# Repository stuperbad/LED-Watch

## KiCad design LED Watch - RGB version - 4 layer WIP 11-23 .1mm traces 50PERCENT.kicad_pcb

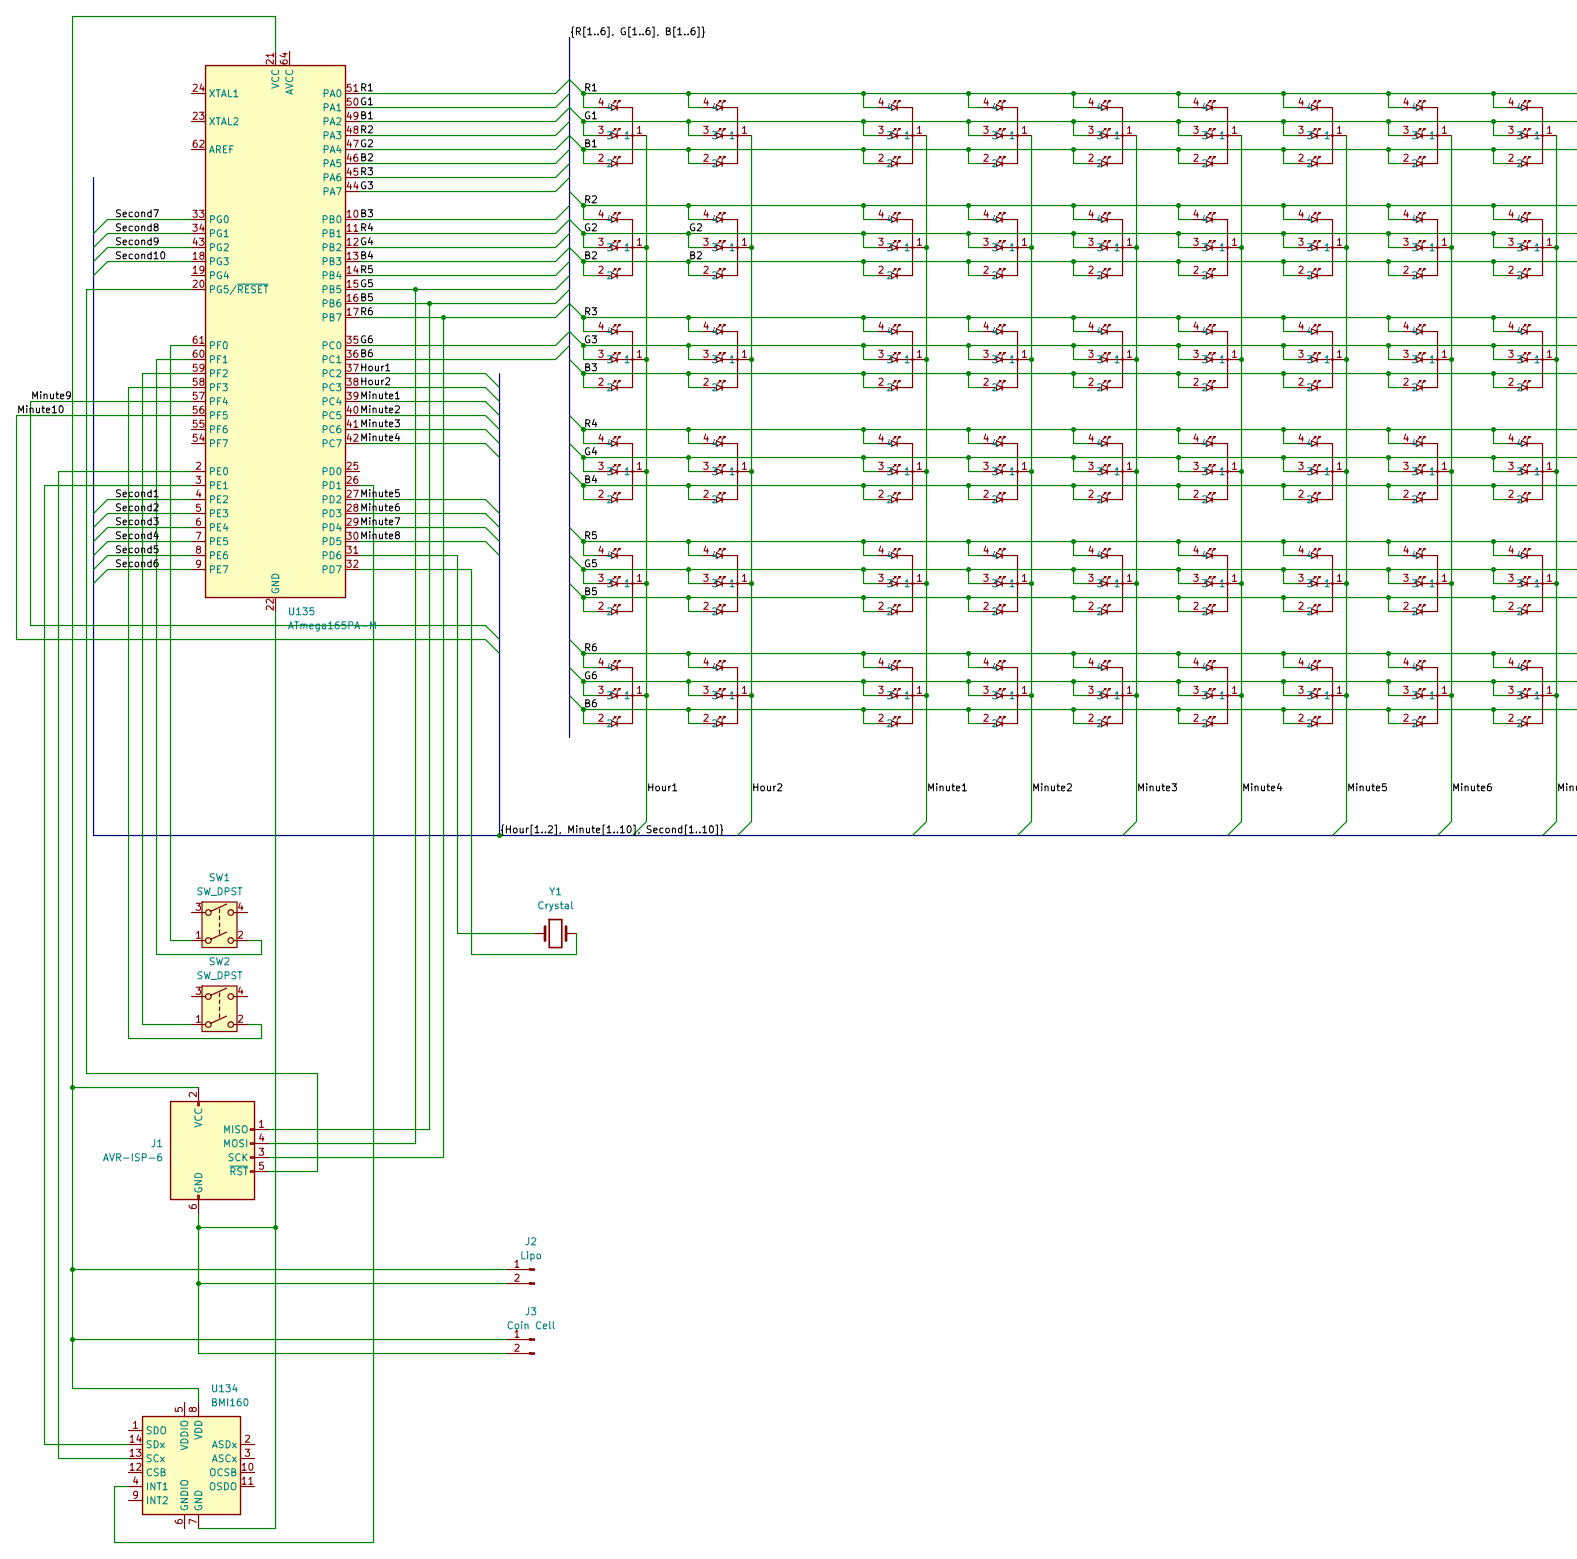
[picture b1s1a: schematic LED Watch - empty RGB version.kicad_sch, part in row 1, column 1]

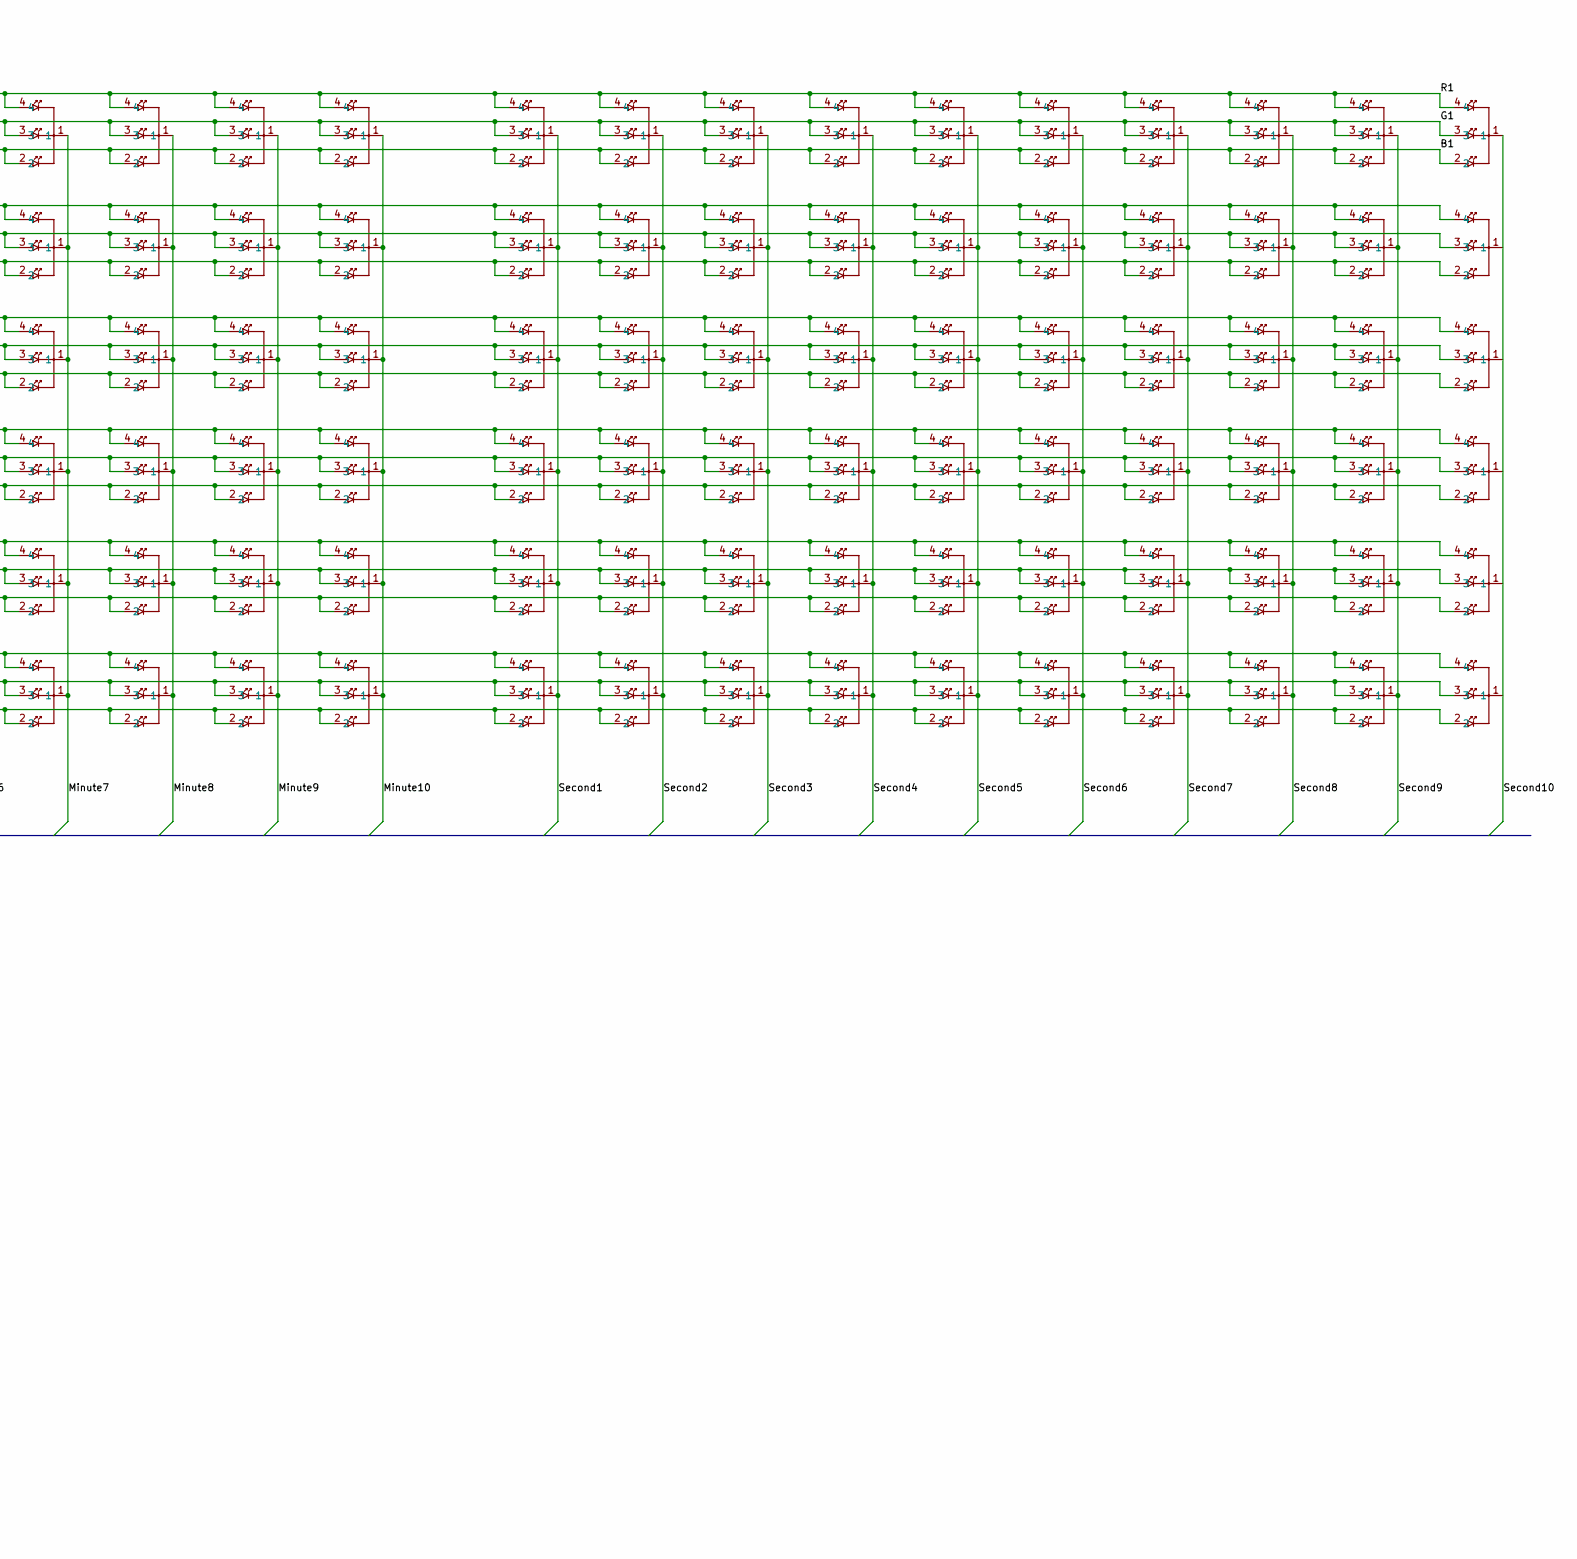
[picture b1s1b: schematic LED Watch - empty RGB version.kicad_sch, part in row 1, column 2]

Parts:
J1: AVR-ISP-6; JST_SH_BM05B-SRSS-TB_1x05-1MP_P1.00mm_Vertical
J2: Lipo; JST_SH_SM02B-SRSS-TB_1x02-1MP_P1.00mm_Horizontal
J3: Coin Cell; BatteryHolder_Keystone_3034_1x20mm
SW1, SW2: SW_DPST; SW_TS21-34-035-BK-260-SMT-TR
U2, U3, U4, U5, U6, U7, U8, U9, U10, U11, U12, U13, U14, U15, U16, U17, U18, U19, U20, U21, U22, U23, U24, U25, U26, U27, U28, U29, U30, U31, U32, U33, U34, U35, U36, U37, U38, U39, U40, U41, U42, U43, U44, U45, U46, U47, U48, U49, U50, U51, U52, U53, U54, U55, U56, U57, U58, U59, U60, U61, U62, U63, U64, U65, U66, U67, U68, U69, U70, U71, U72, U73, U74, U75, U76, U77, U78, U79, U80, U81, U82, U83, U84, U85, U86, U87, U88, U89, U90, U91, U92, U93, U94, U95, U96, U97, U98, U99, U100, U101, U102, U103, U104, U105, U106, U107, U108, U109, U110, U111, U112, U113, U114, U115, U116, U117, U118, U119, U120, U121, U122, U123, U124, U125, U126, U127, U128, U129, U130, U131, U132, U133: B39D3RGB-F6C0001HOU1930; B39D3RGB-F6C0001HOU1930_HVK; MPN LTST-C19HE1WT; Digi-Key_PN 160-2162-1-ND
U134: BMI160; Bosch_LGA-14_3x2.5mm_P0.5mm
U135: ATmega165PA-M; QFN-64-1EP_9x9mm_P0.5mm_EP5.4x5.4mm
Y1: Crystal; Crystal_SMD_3215-2Pin_3.2x1.5mm

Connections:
/B1: U2.2, U8.2, U14.2, U20.2, U26.2, U32.2, U38.2, U44.2, U50.2, U56.2, U62.2, U68.2, U74.2, U80.2, U86.2, U92.2, U98.2, U104.2, U110.2, U116.2, U122.2, U128.2, U135.49 (PA2)
/B2: U3.2, U9.2, U15.2, U21.2, U27.2, U33.2, U39.2, U45.2, U51.2, U57.2, U63.2, U69.2, U75.2, U81.2, U87.2, U93.2, U99.2, U105.2, U111.2, U117.2, U123.2, U129.2, U135.46 (PA5)
/B3: U4.2, U10.2, U16.2, U22.2, U28.2, U34.2, U40.2, U46.2, U52.2, U58.2, U64.2, U70.2, U76.2, U82.2, U88.2, U94.2, U100.2, U106.2, U112.2, U118.2, U124.2, U130.2, U135.10 (PB0)
/B4: U5.2, U11.2, U17.2, U23.2, U29.2, U35.2, U41.2, U47.2, U53.2, U59.2, U65.2, U71.2, U77.2, U83.2, U89.2, U95.2, U101.2, U107.2, U113.2, U119.2, U125.2, U131.2, U135.13 (PB3)
/B5: J1.1 (MISO), U6.2, U12.2, U18.2, U24.2, U30.2, U36.2, U42.2, U48.2, U54.2, U60.2, U66.2, U72.2, U78.2, U84.2, U90.2, U96.2, U102.2, U108.2, U114.2, U120.2, U126.2, U132.2, U135.16 (PB6)
/B6: U7.2, U13.2, U19.2, U25.2, U31.2, U37.2, U43.2, U49.2, U55.2, U61.2, U67.2, U73.2, U79.2, U85.2, U91.2, U97.2, U103.2, U109.2, U115.2, U121.2, U127.2, U133.2, U135.36 (PC1)
/G1: U2.3, U8.3, U14.3, U20.3, U26.3, U32.3, U38.3, U44.3, U50.3, U56.3, U62.3, U68.3, U74.3, U80.3, U86.3, U92.3, U98.3, U104.3, U110.3, U116.3, U122.3, U128.3, U135.50 (PA1)
/G2: U3.3, U9.3, U15.3, U21.3, U27.3, U33.3, U39.3, U45.3, U51.3, U57.3, U63.3, U69.3, U75.3, U81.3, U87.3, U93.3, U99.3, U105.3, U111.3, U117.3, U123.3, U129.3, U135.47 (PA4)
/G3: U4.3, U10.3, U16.3, U22.3, U28.3, U34.3, U40.3, U46.3, U52.3, U58.3, U64.3, U70.3, U76.3, U82.3, U88.3, U94.3, U100.3, U106.3, U112.3, U118.3, U124.3, U130.3, U135.44 (PA7)
/G4: U5.3, U11.3, U17.3, U23.3, U29.3, U35.3, U41.3, U47.3, U53.3, U59.3, U65.3, U71.3, U77.3, U83.3, U89.3, U95.3, U101.3, U107.3, U113.3, U119.3, U125.3, U131.3, U135.12 (PB2)
/G5: J1.4 (MOSI), U6.3, U12.3, U18.3, U24.3, U30.3, U36.3, U42.3, U48.3, U54.3, U60.3, U66.3, U72.3, U78.3, U84.3, U90.3, U96.3, U102.3, U108.3, U114.3, U120.3, U126.3, U132.3, U135.15 (PB5)
/G6: U7.3, U13.3, U19.3, U25.3, U31.3, U37.3, U43.3, U49.3, U55.3, U61.3, U67.3, U73.3, U79.3, U85.3, U91.3, U97.3, U103.3, U109.3, U115.3, U121.3, U127.3, U133.3, U135.35 (PC0)
/Hour1: U2.1, U3.1, U4.1, U5.1, U6.1, U7.1, U135.37 (PC2)
/Hour2: U8.1, U9.1, U10.1, U11.1, U12.1, U13.1, U135.38 (PC3)
/Minute1: U14.1, U15.1, U16.1, U17.1, U18.1, U19.1, U135.39 (PC4)
/Minute2: U20.1, U21.1, U22.1, U23.1, U24.1, U25.1, U135.40 (PC5)
/Minute3: U26.1, U27.1, U28.1, U29.1, U30.1, U31.1, U135.41 (PC6)
/Minute4: U32.1, U33.1, U34.1, U35.1, U36.1, U37.1, U135.42 (PC7)
/Minute5: U38.1, U39.1, U40.1, U41.1, U42.1, U43.1, U135.27 (PD2)
/Minute6: U44.1, U45.1, U46.1, U47.1, U48.1, U49.1, U135.28 (PD3)
/Minute7: U50.1, U51.1, U52.1, U53.1, U54.1, U55.1, U135.29 (PD4)
/Minute8: U56.1, U57.1, U58.1, U59.1, U60.1, U61.1, U135.30 (PD5)
/Minute9: U62.1, U63.1, U64.1, U65.1, U66.1, U67.1, U135.57 (PF4)
/Minute10: U68.1, U69.1, U70.1, U71.1, U72.1, U73.1, U135.56 (PF5)
/R1: U2.4, U8.4, U14.4, U20.4, U26.4, U32.4, U38.4, U44.4, U50.4, U56.4, U62.4, U68.4, U74.4, U80.4, U86.4, U92.4, U98.4, U104.4, U110.4, U116.4, U122.4, U128.4, U135.51 (PA0)
/R2: U3.4, U9.4, U15.4, U21.4, U27.4, U33.4, U39.4, U45.4, U51.4, U57.4, U63.4, U69.4, U75.4, U81.4, U87.4, U93.4, U99.4, U105.4, U111.4, U117.4, U123.4, U129.4, U135.48 (PA3)
/R3: U4.4, U10.4, U16.4, U22.4, U28.4, U34.4, U40.4, U46.4, U52.4, U58.4, U64.4, U70.4, U76.4, U82.4, U88.4, U94.4, U100.4, U106.4, U112.4, U118.4, U124.4, U130.4, U135.45 (PA6)
/R4: U5.4, U11.4, U17.4, U23.4, U29.4, U35.4, U41.4, U47.4, U53.4, U59.4, U65.4, U71.4, U77.4, U83.4, U89.4, U95.4, U101.4, U107.4, U113.4, U119.4, U125.4, U131.4, U135.11 (PB1)
/R5: U6.4, U12.4, U18.4, U24.4, U30.4, U36.4, U42.4, U48.4, U54.4, U60.4, U66.4, U72.4, U78.4, U84.4, U90.4, U96.4, U102.4, U108.4, U114.4, U120.4, U126.4, U132.4, U135.14 (PB4)
/R6: J1.3 (SCK), U7.4, U13.4, U19.4, U25.4, U31.4, U37.4, U43.4, U49.4, U55.4, U61.4, U67.4, U73.4, U79.4, U85.4, U91.4, U97.4, U103.4, U109.4, U115.4, U121.4, U127.4, U133.4, U135.17 (PB7)
/Second1: U74.1, U75.1, U76.1, U77.1, U78.1, U79.1, U135.4 (PE2)
/Second2: U80.1, U81.1, U82.1, U83.1, U84.1, U85.1, U135.5 (PE3)
/Second3: U86.1, U87.1, U88.1, U89.1, U90.1, U91.1, U135.6 (PE4)
/Second4: U92.1, U93.1, U94.1, U95.1, U96.1, U97.1, U135.7 (PE5)
/Second5: U98.1, U99.1, U100.1, U101.1, U102.1, U103.1, U135.8 (PE6)
/Second6: U104.1, U105.1, U106.1, U107.1, U108.1, U109.1, U135.9 (PE7)
/Second7: U110.1, U111.1, U112.1, U113.1, U114.1, U115.1, U135.33 (PG0)
/Second8: U116.1, U117.1, U118.1, U119.1, U120.1, U121.1, U135.34 (PG1)
/Second9: U122.1, U123.1, U124.1, U125.1, U126.1, U127.1, U135.43 (PG2)
/Second10: U128.1, U129.1, U130.1, U131.1, U132.1, U133.1, U135.18 (PG3)
unnamed: J1.2 (VCC), J2.1, J3.1, U134.8 (VDD), U135.21 (VCC), U135.52 (VCC)
unnamed: J1.5 (~RST), U135.20 (PG5/~RESET)
unnamed: U134.4 (INT1), U135.26 (PD1)
unnamed: U134.13 (SCx), U135.2 (PE0)
unnamed: U134.14 (SDx), U135.3 (PE1)
unnamed: SW1.1, U135.61 (PF0)
unnamed: SW1.2, U135.60 (PF1)
unnamed: SW2.1, U135.59 (PF2)
unnamed: SW2.2, U135.58 (PF3)

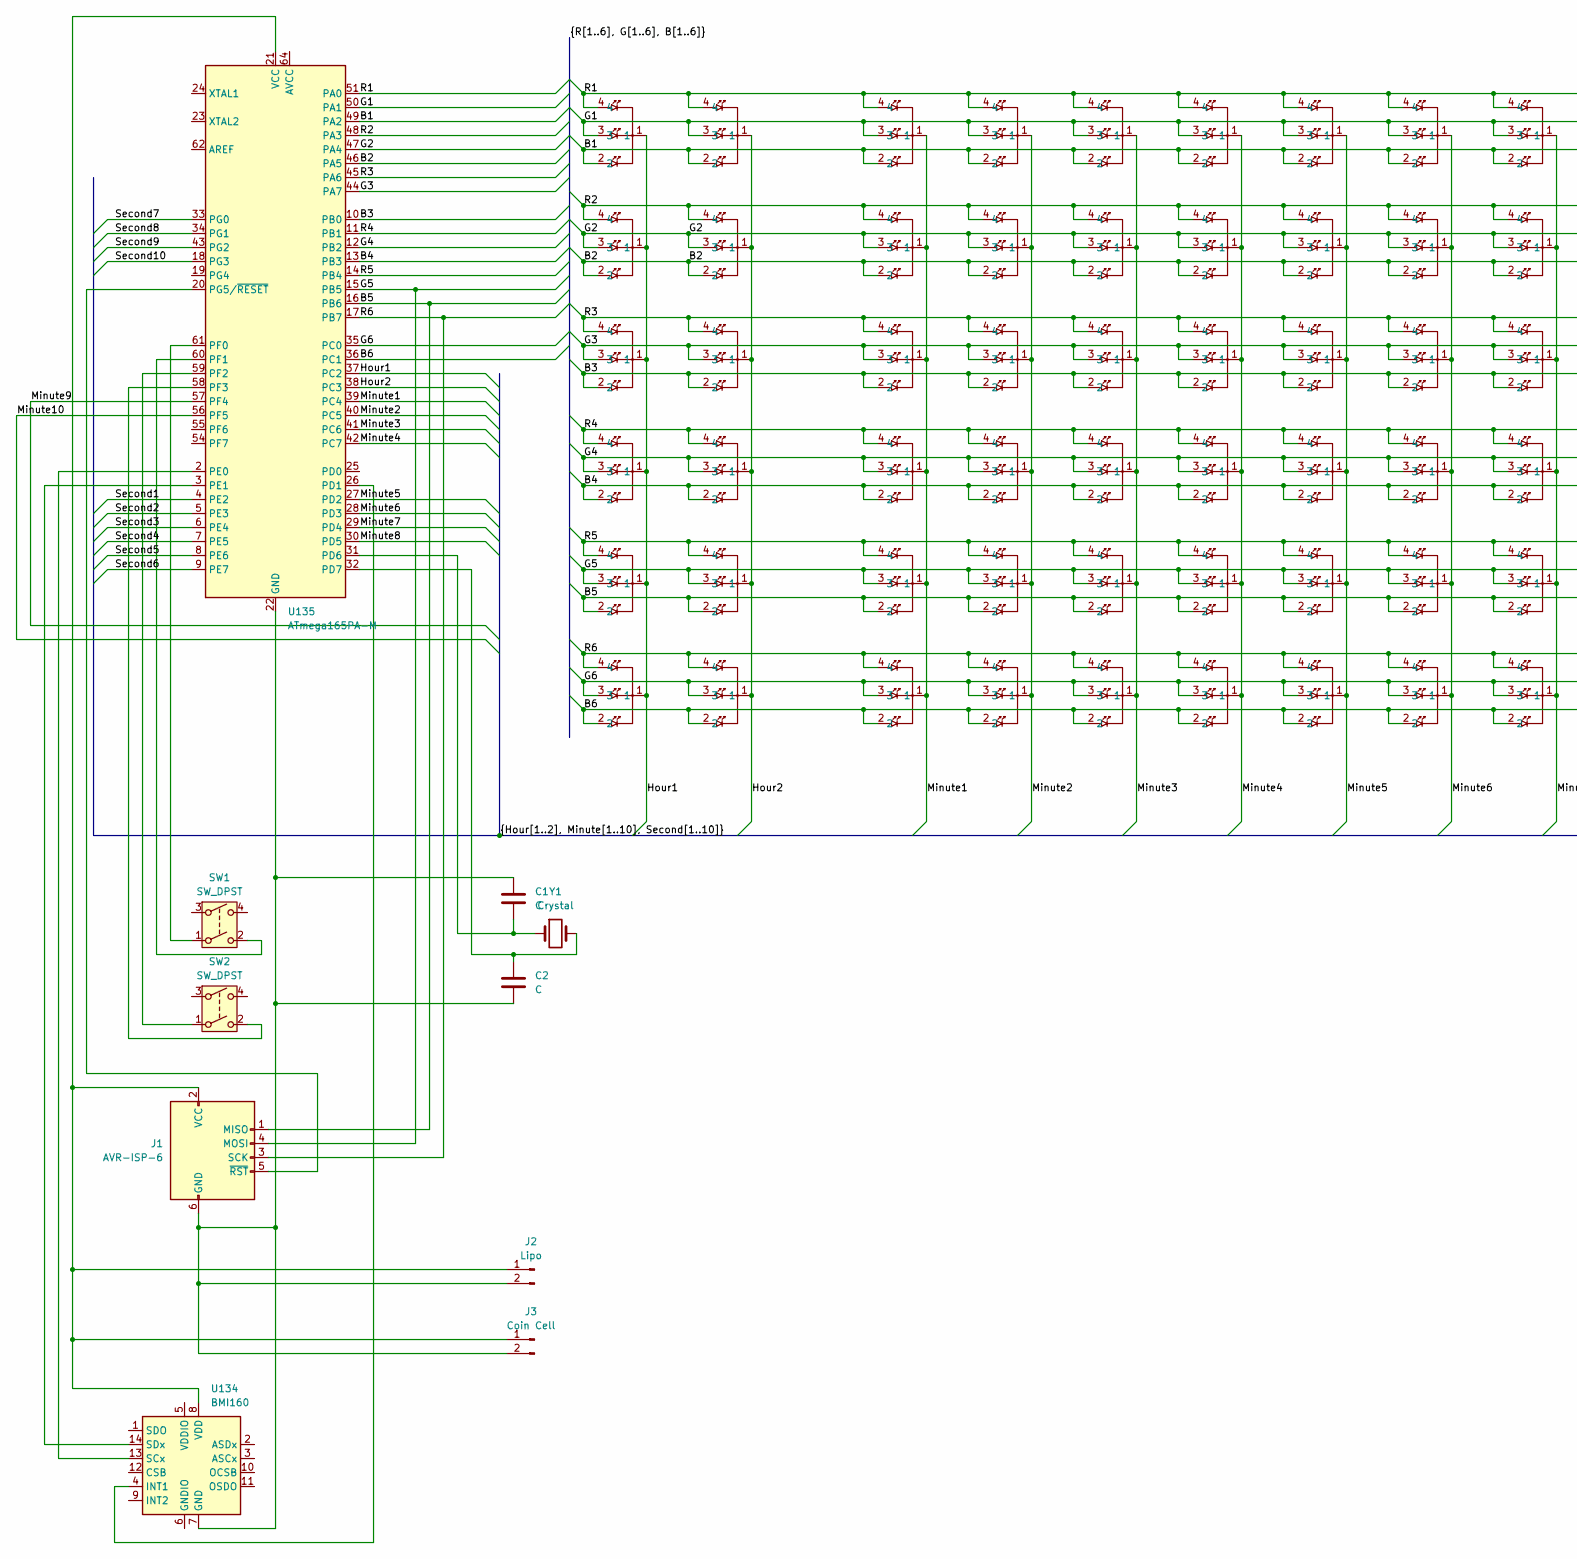
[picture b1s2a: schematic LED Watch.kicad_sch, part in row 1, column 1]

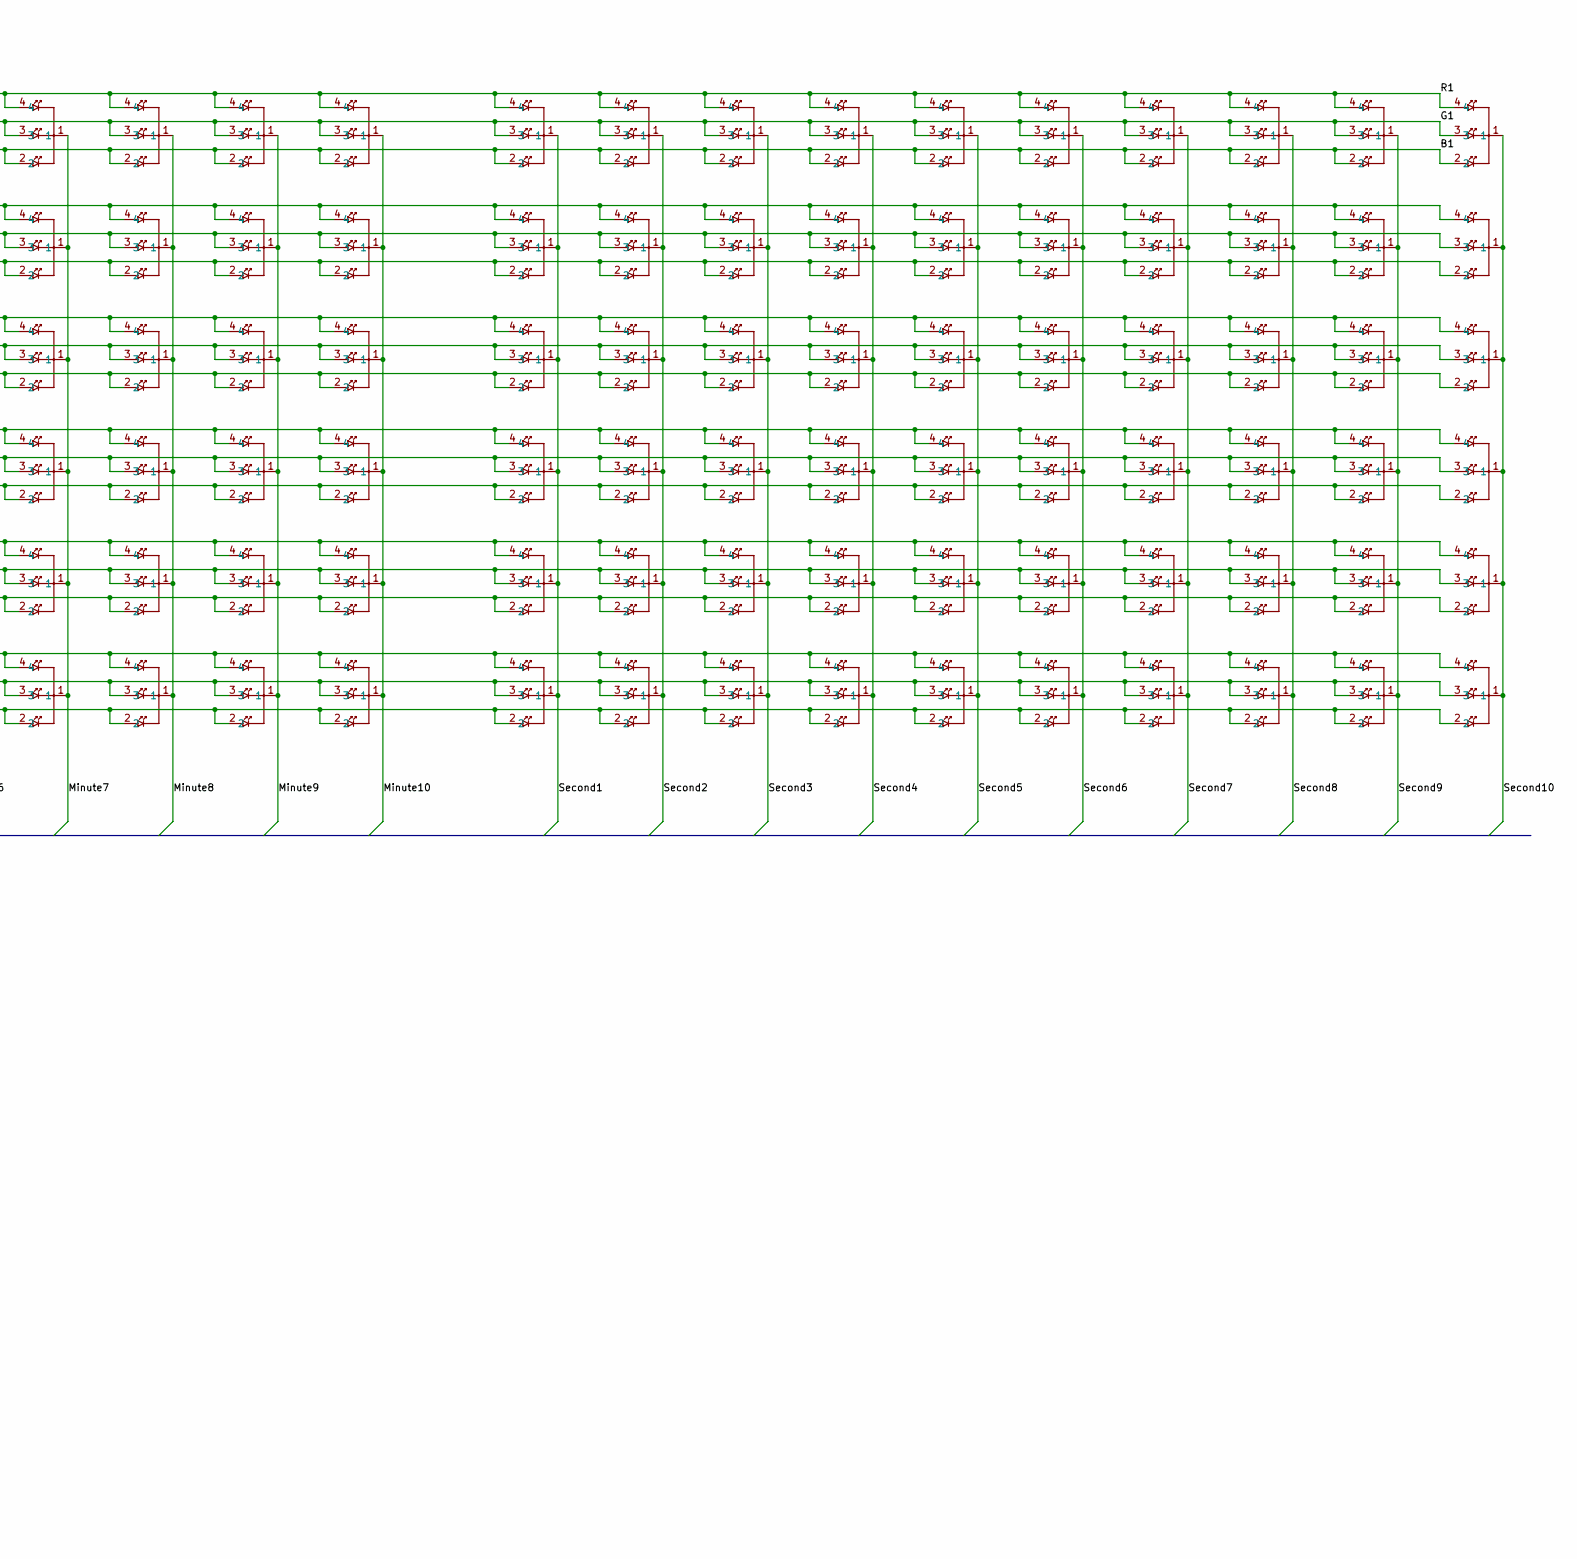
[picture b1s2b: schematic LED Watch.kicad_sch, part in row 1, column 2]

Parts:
C1, C2: C; C_0201_0603Metric
J1: AVR-ISP-6; Tag-Connect_TC2030-IDC-NL_2x03_P1.27mm_Vertical
J2: Lipo; JST_SH_SM02B-SRSS-TB_1x02-1MP_P1.00mm_Horizontal
J3: Coin Cell; BatteryHolder_Keystone_3034_1x20mm
SW1, SW2: SW_DPST; SW_TS21-34-035-BK-260-SMT-TR
U2, U3, U4, U5, U6, U7, U8, U9, U10, U11, U12, U13, U14, U15, U16, U17, U18, U19, U20, U21, U22, U23, U24, U25, U26, U27, U28, U29, U30, U31, U32, U33, U34, U35, U36, U37, U38, U39, U40, U41, U42, U43, U44, U45, U46, U47, U48, U49, U50, U51, U52, U53, U54, U55, U56, U57, U58, U59, U60, U61, U62, U63, U64, U65, U66, U67, U68, U69, U70, U71, U72, U73, U74, U75, U76, U77, U78, U79, U80, U81, U82, U83, U84, U85, U86, U87, U88, U89, U90, U91, U92, U93, U94, U95, U96, U97, U98, U99, U100, U101, U102, U103, U104, U105, U106, U107, U108, U109, U110, U111, U112, U113, U114, U115, U116, U117, U118, U119, U120, U121, U122, U123, U124, U125, U126, U127, U128, U129, U130, U131, U132, U133: B39D3RGB-F6C0001HOU1930; B39D3RGB-F6C0001HOU1930_HVK; MPN LTST-C19HE1WT; Digi-Key_PN 160-2162-1-ND
U134: BMI160; Bosch_LGA-14_3x2.5mm_P0.5mm
U135: ATmega165PA-M; QFN-64-1EP_9x9mm_P0.5mm_EP5.4x5.4mm
Y1: Crystal; Crystal_SMD_3215-2Pin_3.2x1.5mm

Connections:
/B1: U2.2, U8.2, U14.2, U20.2, U26.2, U32.2, U38.2, U44.2, U50.2, U56.2, U62.2, U68.2, U74.2, U80.2, U86.2, U92.2, U98.2, U104.2, U110.2, U116.2, U122.2, U128.2, U135.49 (PA2)
/B2: U3.2, U9.2, U15.2, U21.2, U27.2, U33.2, U39.2, U45.2, U51.2, U57.2, U63.2, U69.2, U75.2, U81.2, U87.2, U93.2, U99.2, U105.2, U111.2, U117.2, U123.2, U129.2, U135.46 (PA5)
/B3: U4.2, U10.2, U16.2, U22.2, U28.2, U34.2, U40.2, U46.2, U52.2, U58.2, U64.2, U70.2, U76.2, U82.2, U88.2, U94.2, U100.2, U106.2, U112.2, U118.2, U124.2, U130.2, U135.10 (PB0)
/B4: U5.2, U11.2, U17.2, U23.2, U29.2, U35.2, U41.2, U47.2, U53.2, U59.2, U65.2, U71.2, U77.2, U83.2, U89.2, U95.2, U101.2, U107.2, U113.2, U119.2, U125.2, U131.2, U135.13 (PB3)
/B5: J1.1 (MISO), U6.2, U12.2, U18.2, U24.2, U30.2, U36.2, U42.2, U48.2, U54.2, U60.2, U66.2, U72.2, U78.2, U84.2, U90.2, U96.2, U102.2, U108.2, U114.2, U120.2, U126.2, U132.2, U135.16 (PB6)
/B6: U7.2, U13.2, U19.2, U25.2, U31.2, U37.2, U43.2, U49.2, U55.2, U61.2, U67.2, U73.2, U79.2, U85.2, U91.2, U97.2, U103.2, U109.2, U115.2, U121.2, U127.2, U133.2, U135.36 (PC1)
/G1: U2.3, U8.3, U14.3, U20.3, U26.3, U32.3, U38.3, U44.3, U50.3, U56.3, U62.3, U68.3, U74.3, U80.3, U86.3, U92.3, U98.3, U104.3, U110.3, U116.3, U122.3, U128.3, U135.50 (PA1)
/G2: U3.3, U9.3, U15.3, U21.3, U27.3, U33.3, U39.3, U45.3, U51.3, U57.3, U63.3, U69.3, U75.3, U81.3, U87.3, U93.3, U99.3, U105.3, U111.3, U117.3, U123.3, U129.3, U135.47 (PA4)
/G3: U4.3, U10.3, U16.3, U22.3, U28.3, U34.3, U40.3, U46.3, U52.3, U58.3, U64.3, U70.3, U76.3, U82.3, U88.3, U94.3, U100.3, U106.3, U112.3, U118.3, U124.3, U130.3, U135.44 (PA7)
/G4: U5.3, U11.3, U17.3, U23.3, U29.3, U35.3, U41.3, U47.3, U53.3, U59.3, U65.3, U71.3, U77.3, U83.3, U89.3, U95.3, U101.3, U107.3, U113.3, U119.3, U125.3, U131.3, U135.12 (PB2)
/G5: J1.4 (MOSI), U6.3, U12.3, U18.3, U24.3, U30.3, U36.3, U42.3, U48.3, U54.3, U60.3, U66.3, U72.3, U78.3, U84.3, U90.3, U96.3, U102.3, U108.3, U114.3, U120.3, U126.3, U132.3, U135.15 (PB5)
/G6: U7.3, U13.3, U19.3, U25.3, U31.3, U37.3, U43.3, U49.3, U55.3, U61.3, U67.3, U73.3, U79.3, U85.3, U91.3, U97.3, U103.3, U109.3, U115.3, U121.3, U127.3, U133.3, U135.35 (PC0)
/Hour1: U2.1, U3.1, U4.1, U5.1, U6.1, U7.1, U135.37 (PC2)
/Hour2: U8.1, U9.1, U10.1, U11.1, U12.1, U13.1, U135.38 (PC3)
/Minute1: U14.1, U15.1, U16.1, U17.1, U18.1, U19.1, U135.39 (PC4)
/Minute2: U20.1, U21.1, U22.1, U23.1, U24.1, U25.1, U135.40 (PC5)
/Minute3: U26.1, U27.1, U28.1, U29.1, U30.1, U31.1, U135.41 (PC6)
/Minute4: U32.1, U33.1, U34.1, U35.1, U36.1, U37.1, U135.42 (PC7)
/Minute5: U38.1, U39.1, U40.1, U41.1, U42.1, U43.1, U135.27 (PD2)
/Minute6: U44.1, U45.1, U46.1, U47.1, U48.1, U49.1, U135.28 (PD3)
/Minute7: U50.1, U51.1, U52.1, U53.1, U54.1, U55.1, U135.29 (PD4)
/Minute8: U56.1, U57.1, U58.1, U59.1, U60.1, U61.1, U135.30 (PD5)
/Minute9: U62.1, U63.1, U64.1, U65.1, U66.1, U67.1, U135.57 (PF4)
/Minute10: U68.1, U69.1, U70.1, U71.1, U72.1, U73.1, U135.56 (PF5)
/R1: U2.4, U8.4, U14.4, U20.4, U26.4, U32.4, U38.4, U44.4, U50.4, U56.4, U62.4, U68.4, U74.4, U80.4, U86.4, U92.4, U98.4, U104.4, U110.4, U116.4, U122.4, U128.4, U135.51 (PA0)
/R2: U3.4, U9.4, U15.4, U21.4, U27.4, U33.4, U39.4, U45.4, U51.4, U57.4, U63.4, U69.4, U75.4, U81.4, U87.4, U93.4, U99.4, U105.4, U111.4, U117.4, U123.4, U129.4, U135.48 (PA3)
/R3: U4.4, U10.4, U16.4, U22.4, U28.4, U34.4, U40.4, U46.4, U52.4, U58.4, U64.4, U70.4, U76.4, U82.4, U88.4, U94.4, U100.4, U106.4, U112.4, U118.4, U124.4, U130.4, U135.45 (PA6)
/R4: U5.4, U11.4, U17.4, U23.4, U29.4, U35.4, U41.4, U47.4, U53.4, U59.4, U65.4, U71.4, U77.4, U83.4, U89.4, U95.4, U101.4, U107.4, U113.4, U119.4, U125.4, U131.4, U135.11 (PB1)
/R5: U6.4, U12.4, U18.4, U24.4, U30.4, U36.4, U42.4, U48.4, U54.4, U60.4, U66.4, U72.4, U78.4, U84.4, U90.4, U96.4, U102.4, U108.4, U114.4, U120.4, U126.4, U132.4, U135.14 (PB4)
/R6: J1.3 (SCK), U7.4, U13.4, U19.4, U25.4, U31.4, U37.4, U43.4, U49.4, U55.4, U61.4, U67.4, U73.4, U79.4, U85.4, U91.4, U97.4, U103.4, U109.4, U115.4, U121.4, U127.4, U133.4, U135.17 (PB7)
/Second1: U74.1, U75.1, U76.1, U77.1, U78.1, U79.1, U135.4 (PE2)
/Second2: U80.1, U81.1, U82.1, U83.1, U84.1, U85.1, U135.5 (PE3)
/Second3: U86.1, U87.1, U88.1, U89.1, U90.1, U91.1, U135.6 (PE4)
/Second4: U92.1, U93.1, U94.1, U95.1, U96.1, U97.1, U135.7 (PE5)
/Second5: U98.1, U99.1, U100.1, U101.1, U102.1, U103.1, U135.8 (PE6)
/Second6: U104.1, U105.1, U106.1, U107.1, U108.1, U109.1, U135.9 (PE7)
/Second7: U110.1, U111.1, U112.1, U113.1, U114.1, U115.1, U135.33 (PG0)
/Second8: U116.1, U117.1, U118.1, U119.1, U120.1, U121.1, U135.34 (PG1)
/Second9: U122.1, U123.1, U124.1, U125.1, U126.1, U127.1, U135.43 (PG2)
/Second10: U128.1, U129.1, U130.1, U131.1, U132.1, U133.1, U135.18 (PG3)
unnamed: J1.2 (VCC), J2.1, J3.1, U134.8 (VDD), U135.21 (VCC), U135.52 (VCC)
unnamed: J1.5 (~RST), U135.20 (PG5/~RESET)
unnamed: U134.4 (INT1), U135.26 (PD1)
unnamed: U134.13 (SCx), U135.2 (PE0)
unnamed: U134.14 (SDx), U135.3 (PE1)
unnamed: SW1.1, U135.61 (PF0)
unnamed: SW1.2, U135.60 (PF1)
unnamed: SW2.1, U135.59 (PF2)
unnamed: SW2.2, U135.58 (PF3)

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
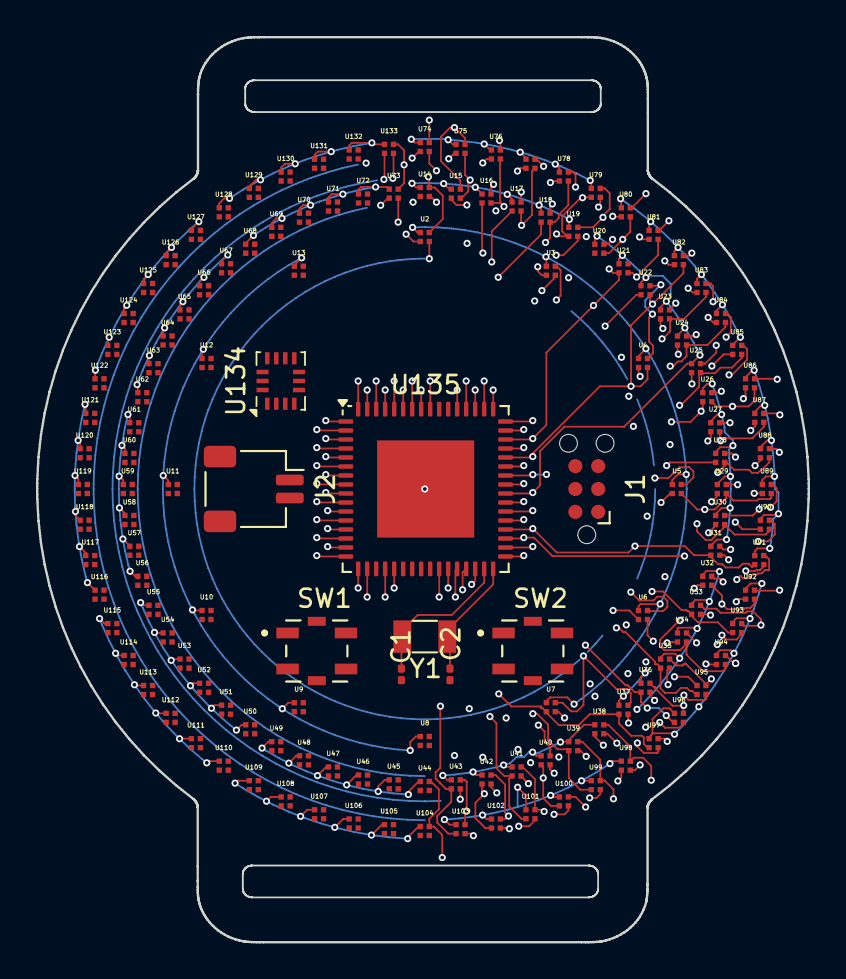
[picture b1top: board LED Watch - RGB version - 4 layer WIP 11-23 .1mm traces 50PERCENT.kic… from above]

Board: 4 copper layers, 42.9 x 50.3 mm, 142 parts (1 on the bottom side), 52 nets.

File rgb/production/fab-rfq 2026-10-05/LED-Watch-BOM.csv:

Comment,Designator,Footprint,Manufacturer Part Number,Source / notes
B39D3RGB-F6C0001HOU1930,"U2,U3,U4,U5,U6,U7,U8,U9,U10,U11,U12,U13,U14,U15,U16,U17,U18,U19,U20,U21,U22,U23,U24,U25,U26,U27,U28,U29,U30,U31,U32,U33,U34,U35,U36,U37,U38,U39,U40,U41,U42,U43,U44,U45,U46,U47,U48,U49,U50,U51,U52,U53,U54,U55,U56,U57,U58,U59,U60,U61,U62,U63,U64,U65,U66,U67,U68,U69,U70,U71,U72,U73,U74,U75,U76,U77,U78,U79,U80,U81,U82,U83,U84,U85,U86,U87,U88,U89,U90,U91,U92,U93,U94,U95,U96,U97,U98,U99,U100,U101,U102,U103,U104,U105,U106,U107,U108,U109,U110,U111,U112,U113,U114,U115,U116,U117,U118,U119,U120,U121,U122,U123,U124,U125,U126,U127,U128,U129,U130,U131,U132,U133",B39D3RGB_F6C0001HOU1930,Harvatek B39D3RGB-F6C0001HOU1930,"DigiKey 3147-B39D3RGB-F6C0001HOU1930CT-ND; 20,772 in stock; $0.197@100 $0.161@500; PART STATUS OBSOLETE (stock until depleted)"
ATMEGA165PA-MU,U135,QFN-64-1EP_9x9mm_P0.5mm,Microchip ATMEGA165PA-MU,DigiKey 1611-ATMEGA165PA-MU-ND; only ~51 in stock when checked; ~$1.65@1
BMI270,U134,Bosch_LGA-14_3x2.5mm_P0.5mm,Bosch BMI270,"DigiKey 828-1091-2-ND; 52,388 in stock. Replaces obsolete BMI160 (same 14-pin LGA 2.5x3.0, identical pin-out - verified in both datasheets)"
32.768kHz crystal,Y1,Crystal_SMD_3215-2Pin_3.2x1.5mm,Abracon ABS07-32.768KHZ-T,CANDIDATE: DigiKey 535-9542-2-ND; 3.2x1.5 mm; 12.5 pF load; 70k ESR; 0.5 uW drive
Capacitor 0201 C0G,"C1,C2",C_0201_0603Metric,TDK C0603C0G1E180J030BA,CANDIDATE: 18 pF 25 V C0G 0201. Value is a rough estimate from 12.5 pF load (~2x(12.5-stray)); EE to confirm
LED 0201,"D1,D2,D3,D4",LED_0201_0603Metric,Kingbright APG0201SEC-TT,"CANDIDATE: orange 605 nm, 2.01 V, 0201 (0.65x0.35 mm). Colour is Evan's choice; other colours exist"
TS21-34-035-BK-260-SMT-TR,"SW1,SW2",SW_TS21-34-035-BK-260-SMT-TR,Same Sky TS21-34-035-BK-260-SMT-TR,"DigiKey 2223-TS21-34-035-BK-260-SMT-TR-ND; 39,050 in stock"
SM02B-SRSS-TB,J2,JST_SH_SM02B-SRSS-TB,JST SM02B-SRSS-TB,"DigiKey 455-SM02B-SRSS-TBTR-ND; 66,088 in stock"
Keystone 3034,J3,BatteryHolder_Keystone_3034,Keystone 3034,"DigiKey 36-3034-ND; 45,006 in stock; BOTTOM side"
